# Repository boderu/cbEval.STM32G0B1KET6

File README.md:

# cbEval.STM32G0B1KET6

Prototypenboard für einen ARM-CortexM0+ Mikrocontroller im Camdenboss-Gehäusesystem.

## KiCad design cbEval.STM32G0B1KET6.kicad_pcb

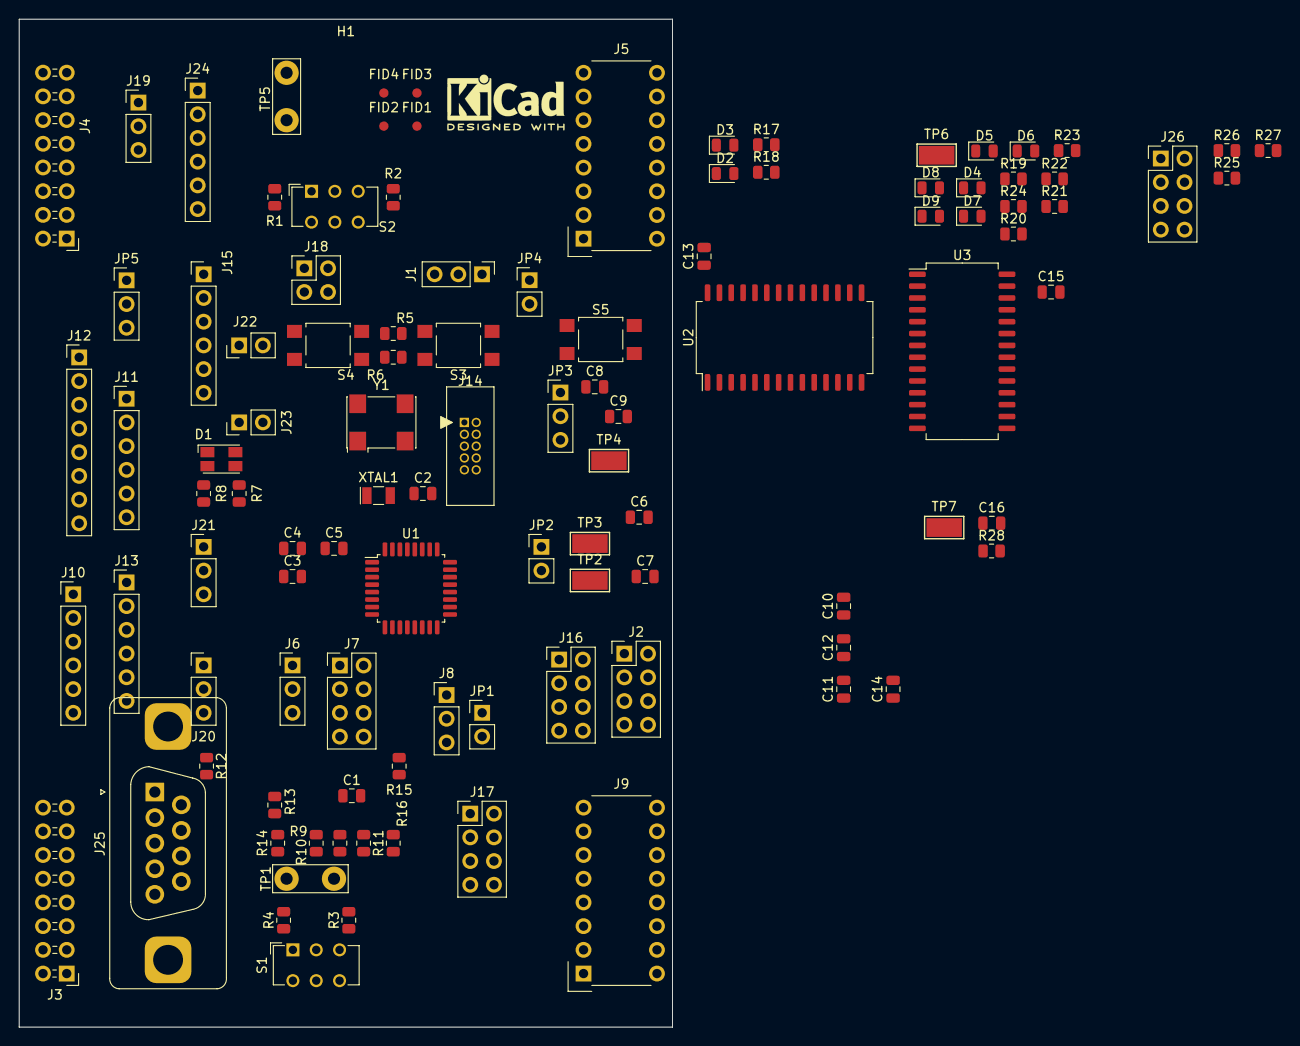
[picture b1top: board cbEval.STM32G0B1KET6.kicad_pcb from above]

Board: 4 copper layers, 70.0 x 108.0 mm, 107 parts (0 on the bottom side), 108 nets, no tracks yet.

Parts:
C1: 4n7; C_0805_2012Metric
C2, C6, C7, C9, C14, C15: 100n; C_0805_2012Metric
C3, C4: 10p; C_0805_2012Metric
C5, C8: 4µ7; C_0805_2012Metric
C10, C11, C12, C13: 1µ(16V); C_0805_2012Metric
C16: 33p; C_0805_2012Metric
D1: E682KRKGWT; LED_Avago_PLCC4_3.2x2.8mm_CW
D2, D3, D6, D7: Würth.VS; LED_0805_2012Metric
D4, D5: Würth.SS; LED_0805_2012Metric
D8, D9: Würth.AS; LED_0805_2012Metric
FID1, FID2, FID3, FID4: 1-2mm; Fiducial_1mm_Mask2mm
H1: CIME.E.BE3500S.2x; Camdenboss.CIME.E.BE3500S.2x
J1, J6, J8, J19, J20, J21: Bergstik-II_3; PinHeader_1x03_P2.54mm_Vertical
J2, J7, J16, J17, J26: Bergstik-II_2x4; PinHeader_2x04_P2.54mm_Vertical
J3, J4: Header.Hor.2x8.9-103326-0-08; PinHeader_2x08_P2.54mm_Horizontal
J5, J9: Socket.Hor.2x8.1-5535512-8; Socket.Hor.2x5.6-5535512-4
J10, J11, J13, J15, J24: Bergstik-II_6; PinHeader_1x06_P2.54mm_Vertical
J12: Bergstik-II_8; PinHeader_1x08_P2.54mm_Vertical
J14: CNC-Tech 2x5; BoxHeader_2x05_P1.27mm_Vertical_3220-10-0100-00
J18: Bergstik-II_2x2; PinHeader_2x02_P2.54mm_Vertical
J22, J23: Bergstik-II_2; PinHeader_1x02_P2.54mm_Vertical
J25: STD.9P.FEM.Vert.Screw; DSUB-9_Female_Vertical_Harting0966151X51X
JP1, JP2, JP4: Bergstik-II_2; PinHeader_1x02_P2.54mm_Vertical
JP3, JP5: Bergstik-II_3; PinHeader_1x03_P2.54mm_Vertical
MP1: KiCAD-DesignedWith-Logo2.5mm.SilkScreen; KiCad-Logo2_5mm_SilkScreen
R1, R2, R3, R10, R13, R14, R16: 10k; R_0805_2012Metric
R4, R5, R6, R9, R15, R25, R26, R27: 4k7; R_0805_2012Metric
R7: 680R; R_0805_2012Metric
R8: 560R; R_0805_2012Metric
R11, R12: 60R4; R_0805_2012Metric
R17, R18, R19, R20, R21, R22, R23, R24: 1k; R_0805_2012Metric
R28: 3k9; R_0805_2012Metric
S1, S2: C&K-JS202011; SW_CuK_JS202011CQN_DPDT_Straight
S3, S4, S5: TL3305A; SW_SPST_TL3305A
TP1, TP5: TAB1287; TestPoint_Bridge_Pitch5.08mm_Drill1.3mm
TP2, TP3, TP4, TP6, TP7: SMT5019; TestPoint_Keystone_5019_Minature
U1: STM32G0B1KET6; LQFP-32_7x7mm_P0.8mm
U2: TRSF3238EIDWR; SOIC-28W_7.5x18.7mm_P1.27mm
U3: MCP23016-I/SO; SOIC-28W_7.5x18.7mm_P1.27mm
XTAL1: CC7VT1A.12P5; Crystal_SMD_MicroCrystal_CC7V-T1A-2Pin_3.2x1.5mm
Y1: 16.000MHz; Oscillator_SMD_Abracon_ASV-4Pin_7.0x5.1mm

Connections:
+3V3: J4.3, J5.3
+5V: J4.5, J5.5
+15V: J4.4, J5.4
+VDC: J4.7, J5.7
-15V: J4.6, J5.6
/Busses/CAN-H: J1.1 (A1), J3.3, J9.3, S1.2 (B)
/Busses/CAN-L: J1.3 (A3), J3.4, J9.4, S1.5 (B)
/Busses/I2C-SCL: J4.10, J5.10, J6.3 (A3), J18.2 (B1), S2.5 (B)
/Busses/I2C-SDA: J4.9, J5.9, J6.2 (A2), J18.4 (B2), S2.2 (B)
/Busses/One-Wire: J3.16, J9.16, J24.6 (A6), R15.2
/Busses/Reserved0: J3.7, J8.1 (A1), J9.7
/Busses/Reserved1: J3.8, J8.3 (A3), J9.8
/Busses/SPI-ADR0: J3.13, J9.13, J17.2 (B1), J19.1 (A1), R1.1
/Busses/SPI-ADR1: J3.14, J9.14, J17.4 (B2), J19.2 (A2), R2.1
/Busses/SPI-ADR2: J3.15, J9.15, J17.6 (B3), J19.3 (A3), R3.1
/Busses/SPI-CLK: J3.11, J9.11, J16.4 (B2), J24.3 (A3), R14.1
/Busses/SPI-MRST: J3.10, J9.10, J16.8 (B4), J24.2 (A2), R13.1
/Busses/SPI-MTSR: J3.9, J9.9, J16.6 (B3), J24.1 (A1), R10.1
/Busses/SPI-~CE: J3.12, J9.12, J16.2 (B1), J24.4 (A4), R16.2
/Busses/~RESET: J4.8, J5.8, J6.1 (A1)
/MCU/I2C-Aux-SCL: J26.2 (B1), R25.2, U3.14 (SCL)
/MCU/I2C-Aux-SDA: J26.4 (B2), R26.2, U3.15 (SDA)
/MCU/I2C-Aux-~INT: J26.8 (B4), R27.2, U3.6 (~INT)
/MCU/PA0: J2.7 (A4), J12.1 (A1), U1.7 (USART2_CTS)
/MCU/PA1: J2.5 (A3), J12.2 (A2), U1.8 (USART2_RTS_DE_CK)
/MCU/PA2: J2.1 (A1), J12.3 (A3), U1.9 (USART2_TX)
/MCU/PA3: J2.3 (A2), J12.4 (A4), U1.10 (USART2_RX)
/MCU/PA4: J12.5 (A5), J16.1 (A1), U1.11 (SPI1_NSS)
/MCU/PA5: J12.6 (A6), J16.3 (A2), U1.12 (SPI1_SCK)
/MCU/PA6: J12.7 (A7), J16.5 (A3), U1.13 (SPI1_MISO)
/MCU/PA7: J12.8 (A8), J16.7 (A4), U1.14 (SPI1_MOSI)
/MCU/PA8: J13.1 (A1), J26.7 (A4), U1.18 (I2C2_SMBA)
/MCU/PA9: J13.2 (A2), J26.1 (A1), U1.19 (I2C2_SCL)
/MCU/PA10: J13.3 (A3), J26.3 (A2), U1.21 (I2C2_SDA)
/MCU/PA11: J13.4 (A4), J17.1 (A1), U1.22 (USB_DM)
/MCU/PA12: J13.5 (A5), J17.3 (A2), U1.23 (USB_DP)
/MCU/PA13: J10.1 (A1), J14.2, U1.24 (SWDIO)
/MCU/PA14: J10.2 (A2), J14.4, U1.25 (SWCLK)
/MCU/PA15: J10.3 (A3), U1.26 (SPI3_NSS)
/MCU/PB0: J7.6 (B3), J11.5 (A5), U1.15 (FDCAN2_RX)
/MCU/PB1: J7.8 (B4), J11.6 (A6), U1.16 (FDCAN2_TX)
/MCU/PB2: J13.6 (A6), J17.5 (A3), U1.17 (PB2)
/MCU/PB3: J10.4 (A4), U1.27 (SPI3_SCK)
/MCU/PB4: J10.5 (A5), U1.28 (SPI3_MISO)
/MCU/PB5: J10.6 (A6), U1.29 (SPI3_MOSI)
/MCU/PB6: J11.1 (A1), J18.1 (A1), U1.30 (I2C1_SCL)
/MCU/PB7: J11.2 (A2), J18.3 (A2), U1.31 (I2C1_SDA)
/MCU/PB8: J7.2 (B1), J11.3 (A3), U1.32 (FDCAN1_RX)
/MCU/PB9: J7.4 (B2), J11.4 (A4), U1.1 (FDCAN1_TX)
/MCU/PC6: J17.7 (A4), U1.20 (PC6(VDDIO2))
/MCU/PF2: C7.1, J14.10, S5.1, U1.6 (~NRST)
/RS-232 Transceiver/DCE-CTS: R20.1, U2.20 (~R2OUT)
/RS-232 Transceiver/DCE-DCD: D8.1 (K), U2.19 (T4IN)
/RS-232 Transceiver/DCE-DSR: D6.1 (K), U2.22 (T3IN)
/RS-232 Transceiver/DCE-DTR: D7.1 (K), U2.18 (~R3OUT)
/RS-232 Transceiver/DCE-RI: D9.1 (K), U2.17 (T5IN)
/RS-232 Transceiver/DCE-RTS: R19.1, U2.23 (T2IN)
/RS-232 Transceiver/DCE-RxD: D3.1 (K), U2.21 (~R1OUT)
/RS-232 Transceiver/DCE-TxD: D2.1 (K), U2.24 (T1IN)
/RS-232 Transceiver/DTE-CTS: J25.8, U2.6 (~T2OUT)
/RS-232 Transceiver/DTE-DCD: J25.1, U2.10 (~T4OUT)
/RS-232 Transceiver/DTE-DSR: J25.6, U2.7 (~T3OUT)
/RS-232 Transceiver/DTE-DTR: J25.4, U2.11 (R3IN)
/RS-232 Transceiver/DTE-RI: J25.9, U2.12 (~T5OUT)
/RS-232 Transceiver/DTE-RTS: J25.7, U2.9 (R2IN)
/RS-232 Transceiver/DTE-RxD: J25.2, U2.5 (~T1OUT)
/RS-232 Transceiver/DTE-TxD: J25.3, U2.8 (R1IN)
/RS-232 Transceiver/~Invalid: TP6.1, U2.15 (~INVALID)
GND: C1.2, C2.2, C3.2, C4.2, C5.2, C6.2, C7.2, C8.2, C9.2, C11.2, C12.2, C14.2, C15.2, C16.2, D4.1 (K), D5.1 (K), J1.2 (A2), J3.1, J3.2, J3.5, J3.6, J4.11, J4.12, J4.13, J4.14, J4.15, J4.16, J5.11, J5.12, J5.13, J5.14, J5.15, J5.16, J8.2 (A2), J9.1, J9.2, J9.5, J9.6, J14.3, J14.5, J14.9, J15.1 (A1), J15.2 (A2), J15.3 (A3), J15.4 (A4), J15.5 (A5), J15.6 (A6), J24.5 (A5), J25.0 (PAD), J25.5, JP5.3 (B), R1.2, R2.2, R3.2, R10.2, R13.2, R14.2, S3.2, S4.2, S5.2, TP1.1, TP5.1, U1.5 (VSS/VSSA), U2.2 (GND), U3.1 (VSS), U3.8 (VSS), U3.16 (A0), U3.17 (A1), U3.18 (A2), U3.19 (VSS), Y1.2 (GND)
unnamed: C1.1, R11.1, R12.1
unnamed: C2.1, C5.1, JP2.1 (A), TP2.1, U1.4 (VDD/VDDA)
unnamed: C3.1, JP3.3 (B), XTAL1.1
unnamed: C4.1, JP4.2 (B), XTAL1.2
unnamed: C10.1, U2.28 (C1+)
unnamed: C10.2, U2.25 (C1-)
unnamed: C11.1, U2.27 (V+)
unnamed: C12.1, U2.4 (V-)
unnamed: C13.1, U2.1 (C2+)
unnamed: C13.2, U2.3 (C2-)
unnamed: C16.1, R28.2, U3.9 (CLK)
unnamed: D1.1 (Rd-C), J23.1 (A1)
unnamed: D1.2 (Rd-A), R7.2
unnamed: D1.3 (Gn-C), J23.2 (A2)
unnamed: D1.4 (Gn-A), R8.2
unnamed: D2.2 (A), R17.2
unnamed: D3.2 (A), R18.2
unnamed: D4.2 (A), R19.2
unnamed: D5.2 (A), R20.2
unnamed: D6.2 (A), R21.2
unnamed: D7.2 (A), R22.2
unnamed: D8.2 (A), R23.2
unnamed: D9.2 (A), R24.2
unnamed: J20.1 (A1), J20.2 (A2), J20.3 (A3)
unnamed: J21.1 (A1), J21.2 (A2), J21.3 (A3)
unnamed: J22.1 (A1), R5.2, S3.1
unnamed: J22.2 (A2), R6.2, S4.1
unnamed: JP1.2 (B), R15.1
unnamed: JP3.1 (A), Y1.3 (Out)
unnamed: JP3.2 (C), TP4.1, U1.2 (OSC32_IN)
unnamed: JP4.1 (A), U1.3 (OSC32_OUT)
unnamed: JP5.2 (C), Y1.1 (Enable)
unnamed: R4.1, S2.3 (C)
unnamed: R9.1, S2.6 (C)
unnamed: R11.2, S1.3 (C)
unnamed: R12.2, S1.6 (C)
unnamed: TP7.1, U3.10 (TP)
PwrMCU: C8.1, C9.1, J14.1, J17.8 (B4), JP2.2 (B), R25.1, R26.1, R27.1, TP3.1
VCC: C6.1, C14.1, C15.1, J4.1, J4.2, J5.1, J5.2, JP1.1 (A), JP5.1 (A), R4.2, R5.1, R6.1, R7.1, R8.1, R9.2, R16.1, R17.1, R18.1, R21.1, R22.1, R23.1, R24.1, R28.1, U2.26 (VCC), U3.20 (VDD), Y1.4 (VDD)

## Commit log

2022-02-22 Zwischenstand (Sicherung)
2023-11-08 Update auf KiCAD-Version 7
